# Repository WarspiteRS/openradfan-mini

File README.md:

# OpenRadFan
An ESPHome-driven smart controller for 12V PWM fans.

Classical radiators (K2/K3) typically require relatively high flow temperatures to heat up a room. Using forced convection can significally enhance their efficiency, especially at low flow temperatures. While there are a number of commercial solutions available, these did not need my needs. They are either too loud while running or switching on/off using a relays, don't properly switch at low flow temperatures, are too expensive or simply not powerful enough. Hence, I set out to build my own solution using standard 120/140mm PWM-capable PC fans. High-end fans run at low speeds (<500 RPM) are essentially inaudible and provide a definite boost to the room temperature. Being able to smartly control the fan speed and integrate them into Home Assistant - while not a must - is definitely very nice to have if you want to control fan speed based on time of day, current room temperature or room occupancy. The fans can even be used as a kind of thermostat to modulate room temperature without restricting flow to the radiators, which is especially crucial when using a heat pump that perform best with an open loop circulation and no TRVs.

Using these devices throughout our house, we can run out heat pump at flow temperatures typically reserved for good underfloor heating setups (Vaillant heat curve at 0.25 - 30°C flow temperature at 0°C, 35°C flow temperature at -10°C).

## Features
### Hardware
- M5Stack Atom Lite / Atom Lite S3 pluggable µC with usable Grove port for arbitrary I2C device support
- 8 fan connectors in 2x4 rows *[OpenRadFan-mini only has 2 fan connectors in 2x1 rows]*
- Each row can be individually PWM controlled (this is not enabled by default)
- RPM measurement for the first fan in each row *[OpenRadFan-mini only has one fan in each row]*
- Global on/off switch for fans that don't support zero output at zero PWM
- Plug-in connector for two DS18B20-compatible temperature sensors *[OpenRadFan-mini only has one temperature sensor]*
- Power supply: 12V barrel jack (2.1/2.5 mm), center positive
- Reverse voltage & transient overvoltage protection, 2.5 A resettable fuse
### Software
- Fully ESPHome compatible
- Controllable via Home Assistant or through any browser via stand-alone webserver
- Automatic fan curve driven speed control
- Setup & Connection to local WiFi via improv WiFi Hotspot on first boot

## Set-up instructions
**Don't connect to USB when the Atom lite is plugged into the PCB - there is no mechanism to block voltages between the included buck converter and the computer.**
1. Compile & flash ESPHome firmware on the Atom Lite using USB. Skip this step if you have a pre-flashed controller. The ESPHome directory on GitHub contains the yaml as well as factory & ota images so you can directly flash this without a local ESPHome compiler set up.
2. Connect DS18B20 to the push-in terminal block. The wire designations are marked on the PCB and are (from left to right): +3.3V, Data, GND. It's easiest to insert them all at the same time. Hold the wires in one hand in the correct order and insert them into the terminal. Then push all orange levers down at the same time and push the wires down as far as possible. The levers should almost return to the initial position and not be stuck halfway down. If you want to use more than one sensor, you need to manually edit the ESPHome yaml and include the individual IDs of the DS18B20s.

4. Plug in the Atom Lite controller module and fans.
5. Lastly, plug in the barrel plug to power the device
6. On first boot, the device will present a hotspot named "openradfan-xxxxxx", with xxxxxx being the last characters of the Atom Lite's MAC address. You can connect to it in order to enter your WiFi credentials. The passwort for the hotspot is "OpenRadFan". If you get a warning that the hotspot does not provide an internet connection, click "Yes" when asked to connect anyways. Then, point your browser to http://192.168.4.1 to open the config page. Tap/click on your home WiFi and enter the password. Note down the hostname shown after "Wifi Networks:" (here "openradfan-f9465c"), this is also the hostname you can use to connect to the web interface after it has connected to your Wifi via http://openradfan-xxxxxx. It might be required to power cycle if you don't see the device appearing in your network.

8. Home Assistant should automatically detect the device under Settings --> Devices & Services

9. You can adopt it in your local ESPHome environment. The full yaml code will be fethed from GitHub when you do so, so you can adapt the config if needed.
10. The web interface gives you full control over all aspects of the device. Over-the-air (OTA) updates can also be uploaded and flashed to the device.

## Fan curve control
You can set 5 temperature points and associated fan speeds to build a temperature-dependent fan speed response. The speed between the points is interpolated linearly. The temperatures have to increase from 1 to 5; this is also enforced by internal logic. Temperatures above/below the highest/lowest setpoint keep the speed of this setpoint. Set "Auto Fan Curve Control" to on in order to use this feature.

In the below example, the fans are off below 20°C, increase between 0 and 29% speed in the range between 20 and 21°C, then increase up to 100% at 25°C. Above that, speed decreases to 28% at 30°C and the fans are off again at 35°C.

When fan speed is set to zero, the internal high-level switch also cuts all power to the fans. Some fans (e.g. Arctic PXX PWM) turn off with a zero PWM signal and wouldn't need this functionality, however many other fans cannot be turned off via PWM alone.

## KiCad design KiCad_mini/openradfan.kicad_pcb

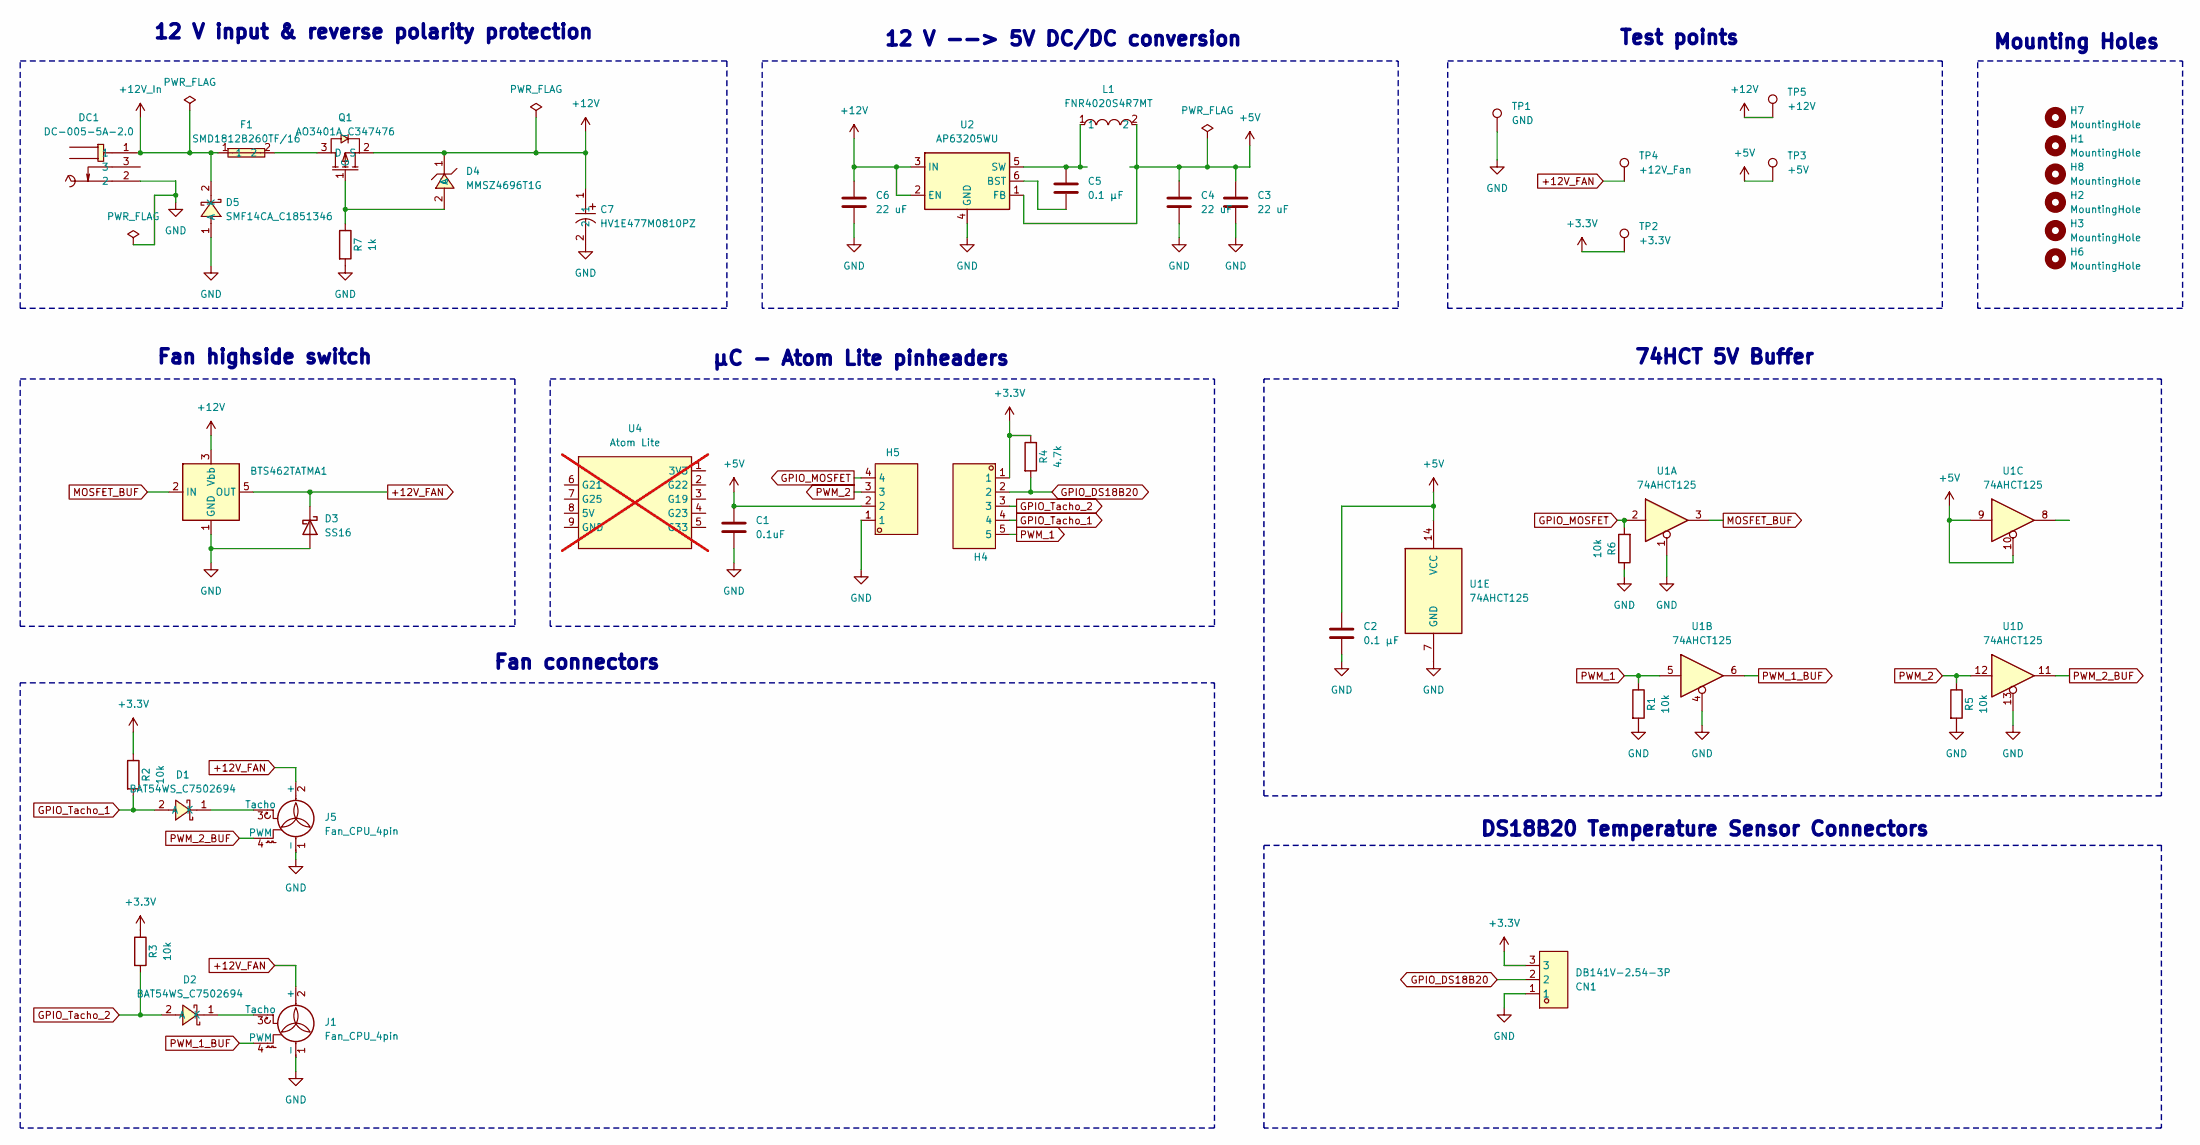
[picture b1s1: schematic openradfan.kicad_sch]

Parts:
C1: 0.1uF; C_0805_2012Metric_Pad1.18x1.45mm_HandSolder; LCSC Part # C28233
C2: 0.1 µF; C_0805_2012Metric_Pad1.18x1.45mm_HandSolder; LCSC Part # C28233
C3, C4, C6: 22 uF; C_1210_3225Metric; LCSC Part # C309062
C5: 0.1 µF; C_0402_1005Metric; LCSC Part # C1525
C7: HV1E477M0810PZ; CAP-SMD_BD8.0-L8.3-W8.3-LS9.3-FD-2; LCSC Part C5246546
CN1: DB141V-2.54-3P; CONN-TH_3P-P2.54_DIBO_DB141V-2.54-3P; LCSC Part C2898745
D1, D2: BAT54WS_C7502694; SOD-323_L1.7-W1.3-LS2.6-RD-1; LCSC Part C7502694
D3: SS16; D_SMA; LCSC Part # C2481
D4: MMSZ4696T1G; SOD-123_L2.7-W1.6-LS3.7-RD-1; LCSC Part C462868
D5: SMF14CA_C1851346; SOD-123_L2.8-W1.8-LS3.7-BI; LCSC Part C41411783
DC1: DC-005-5A-2.0; DC-IN-TH_DC-005-5A-2.0; LCSC Part C381116
F1: SMD1812B260TF/16; F1812; LCSC Part C269148
H1, H2, H7, H8: MountingHole; MountingHole_3.2mm_M3_DIN965
H3, H6: MountingHole; MountingHole_2.2mm_M2_DIN965
H4: 210S-1*5P L=11.6MMGold-plated black; HDR-TH_5P-P2.54-V-M; LCSC Part C124379
H5: Header-Male-2.54_1x4; HDR-TH_4P-P2.54-V-M; LCSC Part C124378
J1, J5: Fan_CPU_4pin; FanPinHeader_1x04_P2.54mm_Vertical; MPN 0470531000; LCSC Part # C240840
L1: FNR4020S4R7MT; IND-SMD_L4.0-W4.0_FNR40XXS; LCSC Part C167828
Q1: AO3401A_C347476; SOT-23_L2.9-W1.3-P1.90-LS2.4-BR; LCSC Part C347476
R1, R2, R3, R5, R6: 10k; R_0805_2012Metric_Pad1.20x1.40mm_HandSolder; LCSC Part # C17414
R4: 4.7k; R_0805_2012Metric_Pad1.20x1.40mm_HandSolder; LCSC Part # C17673
R7: 1k; R_0603_1608Metric; LCSC Part # C21190
TP1: GND; TestPoint_Keystone_5000-5004_Miniature
TP2: +3.3V; TestPoint_Keystone_5000-5004_Miniature
TP3: +5V; TestPoint_Keystone_5000-5004_Miniature
TP4: +12V_Fan; TestPoint_Keystone_5000-5004_Miniature
TP5: +12V; TestPoint_Keystone_5000-5004_Miniature
U1: 74AHCT125; SOIC-14_3.9x8.7mm_P1.27mm; MPN SN74AHCT125N; LCSC Part # C352957
U2: AP63205WU; TSOT-23-6; LCSC Part # C2071056
U3: BTS462TATMA1; TO-252-4; LCSC Part # C3232325
U4: Atom Lite; not fitted

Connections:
+3.3V: CN1.3, H4.1, R2.1, R3.1, R4.1, TP2.1
+5V: C1.1, C2.1, C3.1, C4.1, H5.2, L1.2, TP3.1, U1.9, U1.10, U1.14 (VCC), U2.1 (FB)
+12V: C6.1, C7.1, D4.1 (C), Q1.2 (S), TP5.1, U2.2 (EN), U2.3 (IN), U3.3 (Vbb)
+12V_FAN: D3.1 (K), J1.2 (+), J5.2 (+), TP4.1, U3.5 (OUT)
+12V_In: D5.2 (K), DC1.1, F1.1
GND: C1.2, C2.2, C3.2, C4.2, C6.2, C7.2, CN1.1, D3.2 (A), D5.1 (A), DC1.2, H5.1, J1.1 (-), J5.1 (-), R1.2, R5.2, R6.1, R7.2, TP1.1, U1.1, U1.4, U1.7 (GND), U1.13, U2.4 (GND), U3.1 (GND)
GPIO_DS18B20: CN1.2, H4.2, R4.2
GPIO_MOSFET: H5.4, R6.2, U1.2
GPIO_Tacho_1: D1.2 (A), H4.4, R2.2
GPIO_Tacho_2: D2.2 (A), H4.3, R3.2
MOSFET_BUF: U1.3, U3.2 (IN)
unnamed: D1.1 (K), J5.3 (Tacho)
unnamed: D2.1 (K), J1.3 (Tacho)
unnamed: D4.2 (A), Q1.1 (G), R7.1
unnamed: F1.2, Q1.3 (D)
unnamed: C5.2, U2.6 (BST)
unnamed: C5.1, L1.1, U2.5 (SW)
PWM_1: H4.5, R1.1, U1.5
PWM_1_BUF: J1.4 (PWM), U1.6
PWM_2: H5.3, R5.1, U1.12
PWM_2_BUF: J5.4 (PWM), U1.11

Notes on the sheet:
12 V input & reverse polarity protection
12 V --> 5V DC/DC conversion
µC - Atom Lite pinheaders
Fan connectors
Mounting Holes
74HCT 5V Buffer
Test points
Fan highside switch
DS18B20 Temperature Sensor Connectors

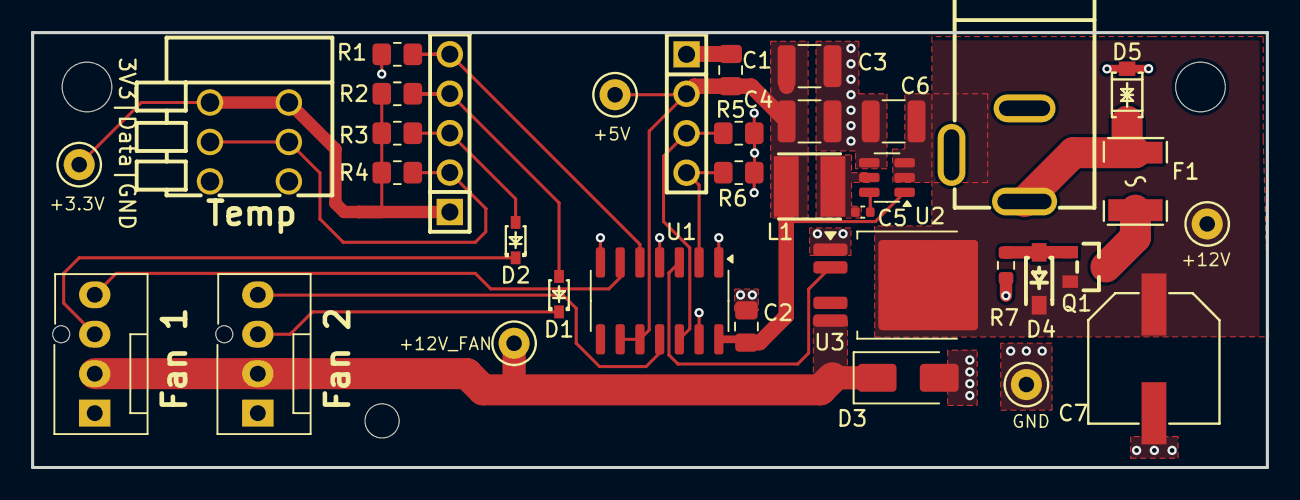
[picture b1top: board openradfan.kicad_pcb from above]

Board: 2 copper layers, 79.5 x 28.0 mm, 39 parts (0 on the bottom side), 21 nets.

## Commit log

2025-02-11 Create openradfan-controller.yaml
    Added initial ESPHome YAML code
2025-02-11 Added package import URL to adopt device
2025-02-11 Removed room name
2025-02-11 Fixed accidental yaml typos
2025-02-13 Include I2C, commented out SCD4x code for reference
2025-02-13 Added exported STEP file
2025-02-13 Update README.md to include full tutorial.
2025-02-13 Added some extra tutorial info
2025-02-13 Added extra image.
2025-02-13 Added ota image
2025-02-13 Added factory image
2025-02-13 Included safety components
    Include reverse voltage protection, transient overvoltage protection & a resettable fuse
2025-03-03 Create m5stack-atom-lite.h to fix unwanted button triggers
2025-03-15 Simplify debugging
    - Store values of power on etc.
    - Uptime sensor
    - debugging active
    - Sensor for last reset reason
2025-03-15 Add heap stats to debug sensors
2025-03-15 Fixed debug sensor
2025-03-16 Switched to ESP-IDF framework
    - Fixed save to flash for temperature curve values
    - Reduced sampling rate of DS18B20
    - Turned off I2C by default
    ESP-IDF led to massively more free RAM. Controller appears much more stable.
2025-03-16 Switched web_server to version 3
2025-03-24 Added automatic standalone yaml creation
2025-03-24 Added automatic api and standalone build scripts
2025-07-30 OpenRadFan-mini
2025-07-30 Rename non-mini to full
2025-07-30 Readme changes
2025-07-31 Readme change
2025-07-31 Prototype fixes
2025-07-31 Proto rearrangement
2025-08-01 Tweaks
